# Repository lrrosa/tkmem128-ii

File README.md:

# TKMEM-128 II

Expansão externa de **128 KB (ou 512 KB) de RAM paginada no padrão ZX Spectrum 128**
para **TK90X, TK95 e ZX Spectrum 48K**. Redesenho completo em **KiCad 10**, com
arquivos de fabricação prontos.

> O nome vem da placa brasileira que originou este redesenho, mas o circuito é do
> **Velesoft e nasceu para o ZX Spectrum 48K**. A adaptação de 2012 ao TK usava um
> contato que no Spectrum carrega vídeo; aqui isso foi corrigido, e a placa voltou
> a servir nas duas famílias. Ver [Compatibilidade](#compatibilidade).

> **Estado: placas fabricadas e conferidas eletricamente, ainda não montadas.**
> ERC e DRC estão zerados, a netlist foi conferida contra a intenção de projeto,
> e as duas placas **voltaram da fábrica em setembro de 2026 com todas as ilhas
> aprovadas no teste de continuidade**. O que ainda não foi feito: **montar os
> componentes e ligar num micro real**. Antes de mandar fabricar, leia
> [`docs/ANTES-DE-FABRICAR.md`](docs/ANTES-DE-FABRICAR.md) — há itens que
> dependem de medir peças físicas.
>
> O conector de borda é o **TE/AMP 5645235**, de entrada vertical. As cotas do
> footprint saíram do desenho de cliente e estão no
> [datasheet arquivado](docs/), mas ninguém montou a peça ainda.

---

## Este projeto é uma derivação

Ele não inventa o circuito: junta e redesenha dois trabalhos anteriores.

| Origem | Autor | O que veio de lá |
| --- | --- | --- |
| [**external 128kb upgrade**](https://velesoft.speccy.cz/zx/external_128kb_upgrade/index.htm) (`zx48_to_128-EASY_3`), 2009 | **Velesoft** (Pavel Cimbal, República Tcheca) | O circuito base: as equações do GAL20V8, o latch da porta `0x7FFD` e o esquema de paginação da SRAM, incluindo a extensão de 512K |
| **TKMEM-128**, 2012 | **Luccas Eletrônica** (Eduardo Luccas, Brasil) | A adaptação ao TK90X/TK95: soquete de EPROM com a ROM do Spectrum 128, jumpers de seleção de ROM, a auto-desativação da RAM interna de 32K por um pino livre do barramento, e a divisão em placa principal + expansor |

Créditos também a **Flávio Matsumoto**, que sugeriu o circuito do Velesoft para
os TKs e identificou a caixa Patola PB 085/3, e a **Daniel Jose Viana
(danjovic)**, cujo trabalho documentou as cotas da placa para essa caixa.

E a [**goloskokovic/zx16to128upgrade**](https://github.com/goloskokovic/zx16to128upgrade),
que redistribui o material do Velesoft com o crédito devido. De lá vieram duas
coisas que não estavam aqui: os **pontos de desativação da RAM interna num ZX
Spectrum 48K**, por Issue de placa-mãe (ver
[`docs/PREPARAR-O-TK.md`](docs/PREPARAR-O-TK.md#e-num-zx-spectrum-48k)), e os
arquivos da variante **`EASY_6b`**, que permitiram comparar as duas versões do
circuito original (ver
[`docs/VELESOFT-EASY3-x-EASY6B.md`](docs/VELESOFT-EASY3-x-EASY6B.md)). Nenhum
desses dois foi verificado em bancada por nós.

Este redesenho é distribuído sob **CERN-OHL-S v2** (ver [LICENSE.txt](LICENSE.txt)),
uma licença *fortemente recíproca*: quem fabricar, modificar ou distribuir
precisa disponibilizar as fontes das modificações sob a mesma licença.

---

## O que a placa faz

O ZX Spectrum 128 difere do 48K em três coisas: 128K de RAM em 8 bancos de 16K,
o chip de som AY-3-8912, e o espelhamento da memória de vídeo ("shadow video").
Esta placa entrega **a primeira**. O som AY exige interface separada; o shadow
video é inviável numa interface externa, porque exigiria interceptar a RAM baixa
da ULA dentro do micro.

Na prática a grande maioria dos jogos de 128K funciona — a exceção são os poucos
títulos que dependem do shadow video.

### Mapa de memória

| Faixa | Quem responde |
| --- | --- |
| `0x0000-0x3FFF` | ROM — a interna do micro, ou a 27C256 da placa (jumper) |
| `0x4000-0x7FFF` | RAM baixa **interna do micro** (memória de vídeo da ULA). Não é decodificada aqui |
| `0x8000-0xBFFF` | SRAM externa, **banco 2 fixo** |
| `0xC000-0xFFFF` | SRAM externa, banco selecionado pela porta `0x7FFD` |

Como a SRAM externa cobre `0x8000-0xFFFF`, **os 32 KB superiores de RAM interna
precisam ser desativados** — é a única alteração necessária dentro do micro, e a
única coisa que difere entre TK e ZX Spectrum. Veja
[`docs/PREPARAR-O-TK.md`](docs/PREPARAR-O-TK.md).

> **Sobre a variante `EASY_6b` do Velesoft.** Circula junto com a nossa em
> outros repositórios, e é fácil confundir com uma versão melhor. Não é: a
> serigrafia da placa dela diz `MEMORY UPGRADE FOR ZX 16`. É para um Spectrum de
> **16 KB**, onde a RAM inteira vem de fora — por isso as equações dela também
> decodificam `0x4000-0x7FFF`. **Este projeto deriva da `EASY_3`**; a comparação
> completa, incluindo a conferência do nosso esquemático e do nosso layout contra
> os do Velesoft, está em
> [`docs/VELESOFT-EASY3-x-EASY6B.md`](docs/VELESOFT-EASY3-x-EASY6B.md).

### Porta 0x7FFD

Um `74HCT273` latcheia o barramento de dados quando o GAL detecta a escrita na
porta (`A15=0`, `A5=1`, `A1=0`, `/IORQ` e `/WR` ativos):

| Bit | Sinal | Função |
| --- | --- | --- |
| 0–2 | `BANK0..BANK2` | Banco de RAM em `0xC000` |
| 3 | `VRAM` | Shadow screen — latcheado, **sem uso** nesta arquitetura (disponível em TP1) |
| 4 | `ROMA14` | Seleciona a metade da 27C256 |
| 5 | `DIS128` | Trava a paginação até o reset |
| 6–7 | `BANK3..BANK4` | Extensão 512K (só no modo ZX512) |

A trava do bit 5 é elegante: `DIS128` entra na equação do clock do latch
(`CLK7FFD = ... + DIS128`), então ao ser setado o clock fica preso em nível alto
e o latch nunca mais é acionado.

---

## Compatibilidade

**TK90X, TK95 e ZX Spectrum 48K.** Não é uma promessa vaga: reduz-se a uma regra
que dá para verificar.

O barramento de expansão é o mesmo conector de 2×28 nas duas famílias, mas
**nove contatos não carregam a mesma coisa** em cada uma. Enquanto a placa não
tocar nenhum deles, ela serve nas duas:

| Contato | No TK90X/TK95 | No ZX Spectrum 48K |
| --- | --- | --- |
| 4 | +9 V | USS |
| 7 | N.C. | GND |
| 15 | GND | sinal |
| 16, 17, 18 | livres | **Y, V e U do vídeo componente** |
| 34, 35 | 12 V | difere |
| 37 | **+5 V** | **−5 V** |

Esta placa liga **34 dos 54 contatos, e nenhum é dessa lista.** Alimentação sai
dos contatos 3 (+5 V), 6 e 14 (GND), que são iguais nas duas máquinas.

A verificação é automática, para a afirmação não envelhecer:

```bash
python tools/confere_compatibilidade.py
```

Ele cruza a lista de divergências de `busdef.py` com os contatos que a netlist
realmente usa, e falha se algum aparecer.

> ⚠️ **O que ainda é específico de cada máquina: desativar a RAM interna de 32 KB.**
> Isso não é opcional — sem desativar, a memória do micro colide com a SRAM
> externa em `0x8000-0xFFFF`. No TK é um fio do contato 29 ao pino 10 do IC27;
> num Spectrum o ponto é outro e **depende da Issue da placa-mãe** — os dois
> procedimentos estão em
> [`docs/PREPARAR-O-TK.md`](docs/PREPARAR-O-TK.md#e-num-zx-spectrum-48k).
> Num Spectrum a placa não aciona nada pelo contato 29 — mas **não porque o
> contato seja diferente**: ele é N.C. nas duas máquinas. É porque o
> procedimento publicado para o Spectrum amarra o pino do mod ao +5 V do
> próprio CI, sem trazer fio até o conector. Levar o truque do TK para lá é a
> mesma topologia, e esbarra numa diferença *elétrica* —
> [analisada aqui](docs/PREPARAR-O-TK.md#dava-para-levar-a-auto-desativação-para-o-spectrum).
>
> Não montamos a placa num Spectrum: a compatibilidade acima é do barramento,
> conferida contato a contato, não de bancada — e o ponto interno do Spectrum
> vem de terceiros, também não verificado por nós.

---

## As duas placas

A placa de componentes fica **em pé** dentro da caixa. O conector de borda é
soldado **diretamente nela** — e como esse conector é de entrada vertical
(a placa que entra fica perpendicular à que segura o conector), a fenda dele cai
no plano horizontal e recebe a placa do micro.

Os terminais do conector são **retos** e atravessam a placa, sobrando ~3,18 mm
do outro lado em duas fileiras a 4,85 mm. A **tira de expansão** entra **entre
essas fileiras** — uma passa por cima dela, a outra por baixo — e é soldada
**dos dois lados**. Ela não tem conector nenhum: ilhas de solda nas duas faces
de um extremo, dedos de borda no outro.

O **conector fica fora da caixa Patola**, atravessando o recorte que se abre na
frente dela. Não é escolha estética: no TK e no ZX Spectrum a abertura
`EXPANSION` é **recuada dentro da carcaça**, então a caixa encosta na traseira do
micro e só o conector entra. A placa, por sua vez, assenta rente ao fundo da
caixa.

> No conector, **1..28 fica na fileira de baixo** (junto à aresta inferior da
> placa), igual à fileira inferior da placa do micro; 29..56 fica do lado de
> dentro. É a mesma convenção no TK e no ZX Spectrum, onde essas fileiras são
> chamadas de B e A.
>
> ⚠️ **O lado dos componentes tem que ficar virado para a tira de expansão**,
> nunca para o lado do conector. Ao contrário, a placa dentro da caixa esbarra
> no micro e não encaixa direito. Na prática o conector de borda é **o único
> componente do lado do cobre**: entra por baixo e é soldado por cima.

| Placa | Arquivo | Conteúdo |
| --- | --- | --- |
| Principal | [`hardware/tkmem128-ii.kicad_pro`](hardware/) | GAL20V8B, 74HCT273, SRAM DIP-32, EPROM 27C256, 3 jumpers, desacoplamento e o conector de borda |
| Tira de expansão | [`hardware/expansor/`](hardware/expansor/) | Ilhas de solda nas duas faces de um lado, dedos de borda do outro — nenhum componente, só o fio de terra `W1` |

A **placa principal é de 4 camadas**; a tira de expansão, de 2.

| Camada | Placa principal | Tira |
| --- | --- | --- |
| F.Cu | sinal | 27 retas de 1,5 mm (pinos 29..56) |
| In1.Cu | **plano de GND** inteiro | — |
| In2.Cu | **plano de +5V** inteiro | — |
| B.Cu | sinal | 27 retas de 1,5 mm (pinos 1..28) |

Como todos os componentes são passantes, cada ilha de `+5V` e de `GND` toca o seu
plano direto: **não há uma única trilha de alimentação nas faces de sinal**, e
nenhuma via serve só para alimentação. Sinal de 0,5 mm, isolação de 0,2 mm,
21 vias, e nenhum fio de ligação.

O furo grande no topo é o `H1`, e ele não é furo de parafuso: por ali **passa a
torre** de fixação da caixa Patola, que tem Ø5 externo e nasce do fundo da
tampa. O parafuso da caixa corre dentro da torre e nunca toca a placa — `H1`
serve para localizar, não para apertar.

O conector é passante e é usado pelos dois lados — por baixo entra o conector,
por cima solda a tira —, então a numeração dele está serigrafada nas duas
faces.

O verso é o manual da placa. Traz as **três tabelas de jumper**, a função do
`R4` e a licença — na bancada, com um shunt na pinça, isso vale mais que este
README.

A tira é soldada dos dois lados, então cada face traz a numeração dos **seus**
pinos: 29..56 na frente, 1..28 no verso.

### E fabricadas

Primeira tiragem, setembro de 2026. **Todas as ilhas passaram no teste de
continuidade** — as placas ainda não foram montadas nem ligadas num micro.

O verso cumpriu o que o render prometia: as três tabelas de jumper e a nota do
`R4` ficam legíveis a olho nu com a serigrafia de 1,2 mm — que é o ponto de
tê-las na placa em vez de só aqui.

A tira mostra os dois itens do formulário que **não viajam nos gerbers** (item 0
do [ANTES-DE-FABRICAR](docs/ANTES-DE-FABRICAR.md)) tendo saído certos: os dedos
vieram com **ENIG** e com o **chanfro de 45°**. O entalhe na borda de baixo, à
direita do centro, é o rasgo da guia — aprofundado de 5,0 para 7,0 mm depois da
conferência em papel.

---

## O que mudou em relação ao original

| Melhoria | Motivo |
| --- | --- |
| **Passagem do barramento** (dedos de borda na expansora) | O original ocupava o barramento; agora dá para encadear outros periféricos |
| **Desacoplamento por CI** (100 nF em cada um) + 10 µF de reservatório | O original tinha desacoplamento mínimo |
| **4 camadas com planos de GND e +5V inteiros** | Alimentação sem uma única trilha nas faces de sinal, retorno de corrente curto e imunidade a ruído. O original era de 2 camadas |
| **Jumper JP2 com duas estratégias de ROMCS** | O `ROMCS` do barramento é **ativo em nível alto** para desligar a ROM interna, o oposto da saída `/ROMCS` do GAL. É a explicação mais provável para a ROM 128 do original "funcionar num TK e não em outro". JP2 permite escolher entre acionar pelo GAL ou fixar em nível alto (como fazem os cartuchos da Interface 2), com R5 em série |
| **Auto-desativação sem jumper nenhum** | A original usava o **pino 17**, livre no TK mas **V do vídeo componente no ZX Spectrum** — daí o jumper e o aviso de que a posição errada danifica o micro. Aqui o sinal vai pelo **pino 29**, que é N.C. nas duas máquinas, então o pull-up é permanente e **JP4 deixou de existir**. Ver [a análise](docs/PREPARAR-O-TK.md#por-que-o-pino-29) |
| **GAL com `.jed` pronto e verificado** | O usuário não precisa montar nada: o `.jed` distribuído é gerado das equações deste projeto e conferido fusível a fusível contra o mapa de referência (checksum `C5752`, zero divergências) |
| **Degrau zero na corrente de periféricos** | A tira de expansão solda nos terminais do próprio conector, ficando coplanar com a placa do micro. O periférico seguinte entra no mesmo plano, sem escadinha |
| **Bit N da porta 7FFD no flip-flop N** | O original embaralhava as entradas do latch; aqui a ordem é natural e o esquemático se lê sozinho |
| **Endereços e dados da EPROM 1:1** | Obrigatório (o conteúdo da ROM é fixo) e documentado |
| **Pontos de teste** (`VRAM`, `CLK7FFD`) | Para depurar sem grampear em perna de CI |
| **LED de energia** (opcional) | Diagnóstico imediato |
| **Peças em produção na BOM** | AS6C1008 e ATF20V8B no lugar de peças só encontráveis como estoque antigo |

---

## Configuração dos jumpers

| Jumper | Posição | Efeito |
| --- | --- | --- |
| **JP1** SELECIONA ROM | 1-2 | ROM 128: a EPROM da placa responde em `0x0000-0x3FFF` |
| | 2-3 | ROM interna: EPROM desligada (padrão) |
| **JP2** ROMCS BARRAMENTO | aberto | Usa a ROM interna do micro (padrão) |
| | 1-2 | Aciona `ROMCS` pelo GAL (comportamento da placa original) |
| | 2-3 | Fixa `ROMCS` em nível alto (estilo Interface 2) |
| **JP3** ZX128/ZX512 | aberto | 128K — SRAM `AS6C1008` (padrão) |
| | fechado | 512K — SRAM `AS6C4008` |

Esta tabela está **serigrafada no verso da placa**, uma por jumper, com as
mesmas palavras — ver o render do verso acima.

> ⚠️ **JP1 em 1-2 sem JP2** não faz nada útil: sem desligar a ROM interna, os dois
> chips disputam o barramento de dados. Use os dois juntos ou nenhum.

> **A auto-desativação da RAM não tem jumper.** `R4` mantém o **pino 29** em
> nível 1 permanentemente, e esse pino é N.C. tanto no TK quanto no ZX Spectrum.
> Num Spectrum a placa não faz nada ali; num TK, com o fio interno do pino 29 ao
> pino 10 do IC27, ela desliga os 32 KB. Nada a configurar.

---

## Lista de material

### Placa principal

| Ref | Valor | Encapsulamento | Observação |
| --- | --- | --- | --- |
| U1 | GAL20V8B, **ATF20V8B-15PC** ou PALCE20V8H | DIP-24 300 mil | Grave [`hardware/gal/tkmem128.jed`](hardware/gal/tkmem128.jed) — peças equivalentes em [hardware/gal](hardware/gal/README.md) |
| U2 | 74HCT273 | DIP-20 300 mil | Latch da porta 7FFD |
| U3 | **AS6C1008-55PCN** (128K×8) | DIP-32 600 mil | Ou `AS6C4008-55PCN` (512K×8) no modo ZX512 — outras peças servem, ver [equivalentes](#equivalentes-para-u3-a-sram) |
| U4 | 27C256 | DIP-28 600 mil | **Opcional** — ver seção da ROM |
| R2, R4 | 1 kΩ | axial, vertical | |
| R5 | 0 Ω | axial, vertical | Fio; 100–470 Ω se houver disputa no ROMCS |
| R3 | 2,2 kΩ | axial, vertical | Opcional (LED) |
| C1–C5 | 100 nF cerâmico | disco 5 mm, passo 5 mm | |
| C6 | 10 µF eletrolítico | radial 5 mm, passo 2 mm | |
| D1 | LED 3 mm | | Opcional |
| JP1, JP2 | header 1×3 | passo 2,54 mm | |
| JP3 | header 1×2 | passo 2,54 mm | |
| J1 | **TE/AMP 5645235** — conector de borda 56 vias, entrada vertical | passo 2,54 mm, fileiras a 4,85 mm | Único componente do lado do cobre; recebe os dedos do micro |
| — | soquetes torneados DIP-20/24/28/32 | | Recomendado |

### Equivalentes para U3 (a SRAM)

O projeto não depende de um fabricante. Serve **qualquer SRAM 128K×8 de 5 V em
DIP-32 na pinagem JEDEC de 1 Mbit** — que é a pinagem padrão dessa família:
`/CS1` no 22, `/OE` no 24, `/WE` no 29, `CE2` no 30, `VCC` no 32, `GND` no 16.

| Peça | Fabricante | Situação |
| --- | --- | --- |
| **AS6C1008-55PCN** | Alliance | Da BOM — ainda em produção, a mais fácil de achar nova |
| **HM628128A** (ex.: `HM628128ALP-7`) | Hitachi | Descontinuada; comum como estoque antigo |
| **TC551001** | Toshiba | Descontinuada |
| **KM681000** | Samsung | Descontinuada |
| **CY62128** | Cypress | |
| **IS61C1024 / IS62C1024** | ISSI | O `1024` é 1024 kbit = 1 Mbit, não 1 M×8 |

> ⚠️ **Uma 62256 não serve.** É 32K×8 (256 kbit) em DIP-28 — outra
> capacidade e outro encapsulamento. A confusão é fácil porque a numeração
> parece próxima.

**A única divergência real entre essas peças é o pino 30**, e vale conferir no
datasheet da que você comprou:

| Pino 30 | Funciona? |
| --- | --- |
| `CE2` / `CS2`, ativo alto | **Sim** — é o caso da `AS6C1008` |
| `NC`, não conectado | **Sim** — o sinal é ignorado e o `/CS1` do pino 22 controla sozinho |
| `A17` | Aí é uma 512K×8, não uma 128K — ver abaixo |

Isso funciona porque `/SA17` é uma saída **invertida** do GAL:

```
/SA17 = A14 * A15 * BANK3 * /ZX512
```

Com **JP3 aberto**, o pull-up põe `ZX512` em alto, o produto zera e o pino 30
fica **fixo em nível alto** — exatamente o `CE2` que a memória espera.

> ⚠️ **Com uma 128K×8, JP3 fica aberto — sempre.** Fechado por engano, o
> pino 30 deixa de ser nível fixo e passa a receber `/SA17` paginado: toda vez
> que o software escrever `BANK3=1` na porta `0x7FFD`, o pino cai para nível
> baixo e **desabilita a RAM** em 0xC000. A falha é intermitente e depende do
> jogo, que é o pior tipo de falha para diagnosticar.

**Velocidade é indiferente.** Peças dessa família vão de 55 a 100 ns, e a
3,5 MHz há mais de 500 ns entre o endereço ficar válido e o Z80 amostrar o
dado. Até a mais lenta sobra.

**Procedência importa mais que velocidade.** As descontinuadas circulam como
estoque antigo e SRAM antiga é alvo comum de remarcação. Se o preço for
parecido, prefira a peça em produção.

#### No modo 512 KB

Aí a peça tem que ser uma **512K×8** de verdade — `AS6C4008`, `HM628512`,
`TC554001`, `IS61C4008` — porque o pino 30 passa a ser `A17` e o pino 1, `A18`.
E **JP3 fecha**. Ver [Modo 512 KB](docs/MONTAGEM.md#modo-512-kb).

### Tira de expansão

Não leva componente nenhum, nem conector: os "conectores" são cobre da própria
PCB, e o único item a soldar além das ilhas é um pedaço de fio.

| Ref | O que é | Observação |
| --- | --- | --- |
| J1 | Ilhas de solda nas duas faces, até a borda | Solda nos terminais retos do conector da placa principal, por cima e por baixo |
| J2 | Dedos de borda | Passagem do barramento ao próximo periférico |
| W1 | Fio isolado curto | Liga as duas ilhas `GND - FIO ISOLADO` no verso (pinos 6 e 14); passa por cima das trilhas, por isso isolado |

---

## Montagem

Guias detalhados:

- [`docs/PREPARAR-O-TK.md`](docs/PREPARAR-O-TK.md) — desativar a RAM interna de 32K
- [`docs/MONTAGEM.md`](docs/MONTAGEM.md) — ordem de montagem, guia do conector, caixa
- [`docs/ANTES-DE-FABRICAR.md`](docs/ANTES-DE-FABRICAR.md) — conferências obrigatórias
- [`docs/VELESOFT-EASY3-x-EASY6B.md`](docs/VELESOFT-EASY3-x-EASY6B.md) — as duas variantes do circuito original, e por que este projeto usa a `EASY_3`

Dois pontos que costumam pegar quem monta:

1. **A guia do conector de borda.** O conector de 56 vias vem sem guia. Na
   posição **5/52** você encaixa um pedacinho de PCB (ou material equivalente)
   casando com o rasgo entre os dedos do TK — a placa não tem furos ali,
   porque não há terminal nessa posição. Sem a guia é fácil plugar deslocado
   e danificar o micro.
2. **A tira de expansão é soldada dos dois lados.** Ela entra entre as duas
   fileiras de terminais retos do conector — uma fileira por cima, outra por
   baixo — e as ilhas chegam até a borda, então o terminal encontra cobre
   mesmo se for curto.

---

## Fabricação

Arquivos prontos em [`production/`](production/): Gerber X2, furação Excellon,
BOM e mapa de posições, para as duas placas.

Cada placa tem o seu `gerbers.zip`, que é o arquivo que se envia à fábrica.

| | Placa principal | Tira de expansão |
| --- | --- | --- |
| Camadas | **4** (F.Cu / GND / +5V / B.Cu) | **2** |
| Espessura | 1,6 mm | 1,6 mm |
| Trilha | 0,5 mm | 1,5 mm |
| Isolação | 0,2 mm | 0,25 mm |
| Furo mínimo | 0,3 mm | — (sem furos) |
| Via | 0,8 mm com furo de 0,4 mm | nenhuma |
| Furo não metalizado | 1 × Ø5,4 (`H1`, passagem da torre da caixa) | nenhum |

Tudo folgado dentro da capacidade padrão de fábrica barata — nada aqui entra em
faixa de preço especial, a não ser as 4 camadas da placa principal.

> ⚠️ **Peça 4 camadas para a placa principal.** Se pedir 2 por engano, a fábrica
> descarta os dois planos internos e a placa sai sem alimentação nenhuma — falha
> que não aparece na inspeção visual. Ver
> [ANTES-DE-FABRICAR, item 3b](docs/ANTES-DE-FABRICAR.md).

**A tira de expansão precisa de acabamento em ouro (ENIG) na placa inteira e
chanfro de 45° na borda dos dedos.** Os dedos entram e saem do conector do
periférico seguinte muitos ciclos, e as ilhas de solda do outro extremo também
chegam à borda — HASL descasca nos dois casos. Peça o chanfro explicitamente,
é um item à parte no pedido.

---

## Gravando o GAL

**Já vai pronto**: grave [`hardware/gal/tkmem128.jed`](hardware/gal/tkmem128.jed)
direto no programador. Checksum de fusíveis **`C5752`** — confira no software do
gravador ao abrir o arquivo.

Esse `.jed` não foi copiado de lugar nenhum: é gerado por
[`tools/galgen.py`](tools/galgen.py) a partir das equações deste projeto, e
conferido **fusível a fusível** contra o mapa de referência do projeto do
Velesoft — *zero divergências em 2706 fusíveis*. O fonte em sintaxe GALasm está
em [`tkmem128.pld`](hardware/gal/tkmem128.pld) para quem quiser modificar.

Programadores XGecu (T48/T56) gravam GAL20V8B, ATF20V8B e PALCE20V8H — mas
**escolha no software o dispositivo que você tem de verdade**: o mapa de
fusíveis é o mesmo, o algoritmo de gravação não.

---

## A ROM do Spectrum 128

**A imagem da ROM não está neste repositório** — ela é copyright da Amstrad/Sky.
O hardware (soquete U4 + jumpers) está lá; a imagem você monta com as suas
cópias de `128-0.rom` e `128-1.rom`:

```bash
cat 128-0.rom 128-1.rom > rom_tkmem128_27c256.bin
```

A ordem importa: `A14` da EPROM vem de `ROMA14` (bit 4 da porta 7FFD), então a
ROM 0 (editor do 128) tem que ficar na metade baixa.

Vale dizer que **a ROM é dispensável**: o autor da TKMEM-128 original deixou de
fornecê-la depois de constatar que os jogos de 128K não dependem dela, e que ela
causava incompatibilidades entre unidades diferentes de TK90X.

---

## Estrutura do repositório

```
hardware/
  tkmem128-ii.kicad_pro/.kicad_sch/.kicad_pcb   placa principal
  expansor/                                   tira de expansão
  lib/                                        símbolos e footprints próprios
  gal/                                        fonte e documentação do GAL
production/
  placa-principal/                            gerbers, furação, BOM, posições, PDF
  tira-expansao/                            idem
docs/
  PREPARAR-O-TK.md   MONTAGEM.md   ANTES-DE-FABRICAR.md
  VELESOFT-EASY3-x-EASY6B.md                  comparação com a variante do autor original
  relatorios/                                 saídas de ERC e DRC
tools/                                        geradores do projeto KiCad
```

A biblioteca de símbolos e footprints é **local ao projeto** — nada depende da
versão das bibliotecas do seu KiCad.

O projeto KiCad **nasceu gerado por script** a partir de uma descrição única da
netlist ([`tools/`](tools/)) — é o que garante que esquemático e placa não
divergem — e depois foi refinado à mão no KiCad. A fonte corrente são os
arquivos em `hardware/`; os geradores ficam como registro e ferramenta de apoio.

### Estado da verificação

| Placa | ERC | DRC | Ligações |
| --- | --- | --- | --- |
| Principal | 0 | 0 erros (6 avisos cosméticos) | 0 pendentes |
| Tira de expansão | 0 | 0 erros (4 avisos cosméticos) | 0 pendentes |

A netlist exportada pelo KiCad foi comparada nó a nó com a intenção de projeto
nas duas placas: **74 nets na principal e 53 na tira, zero divergência**.

---

## Licença

Hardware sob **CERN-OHL-S v2** — ver [LICENSE.txt](LICENSE.txt).

```
Copyright Leonardo Rosa e contribuidores.
Derivado de: "external 128kb upgrade" (Velesoft, 2009)
             TKMEM-128 (Luccas Eletrônica, 2012)

Este código-fonte é licenciado sob CERN-OHL-S v2 ou posterior.
Você pode redistribuí-lo e modificá-lo nos termos dessa licença.
Distribuído SEM QUALQUER GARANTIA, incluindo as de COMERCIALIZAÇÃO,
ADEQUAÇÃO A UM FIM ESPECÍFICO E NÃO-VIOLAÇÃO.
Consulte a CERN-OHL-S v2 para os termos aplicáveis.
```

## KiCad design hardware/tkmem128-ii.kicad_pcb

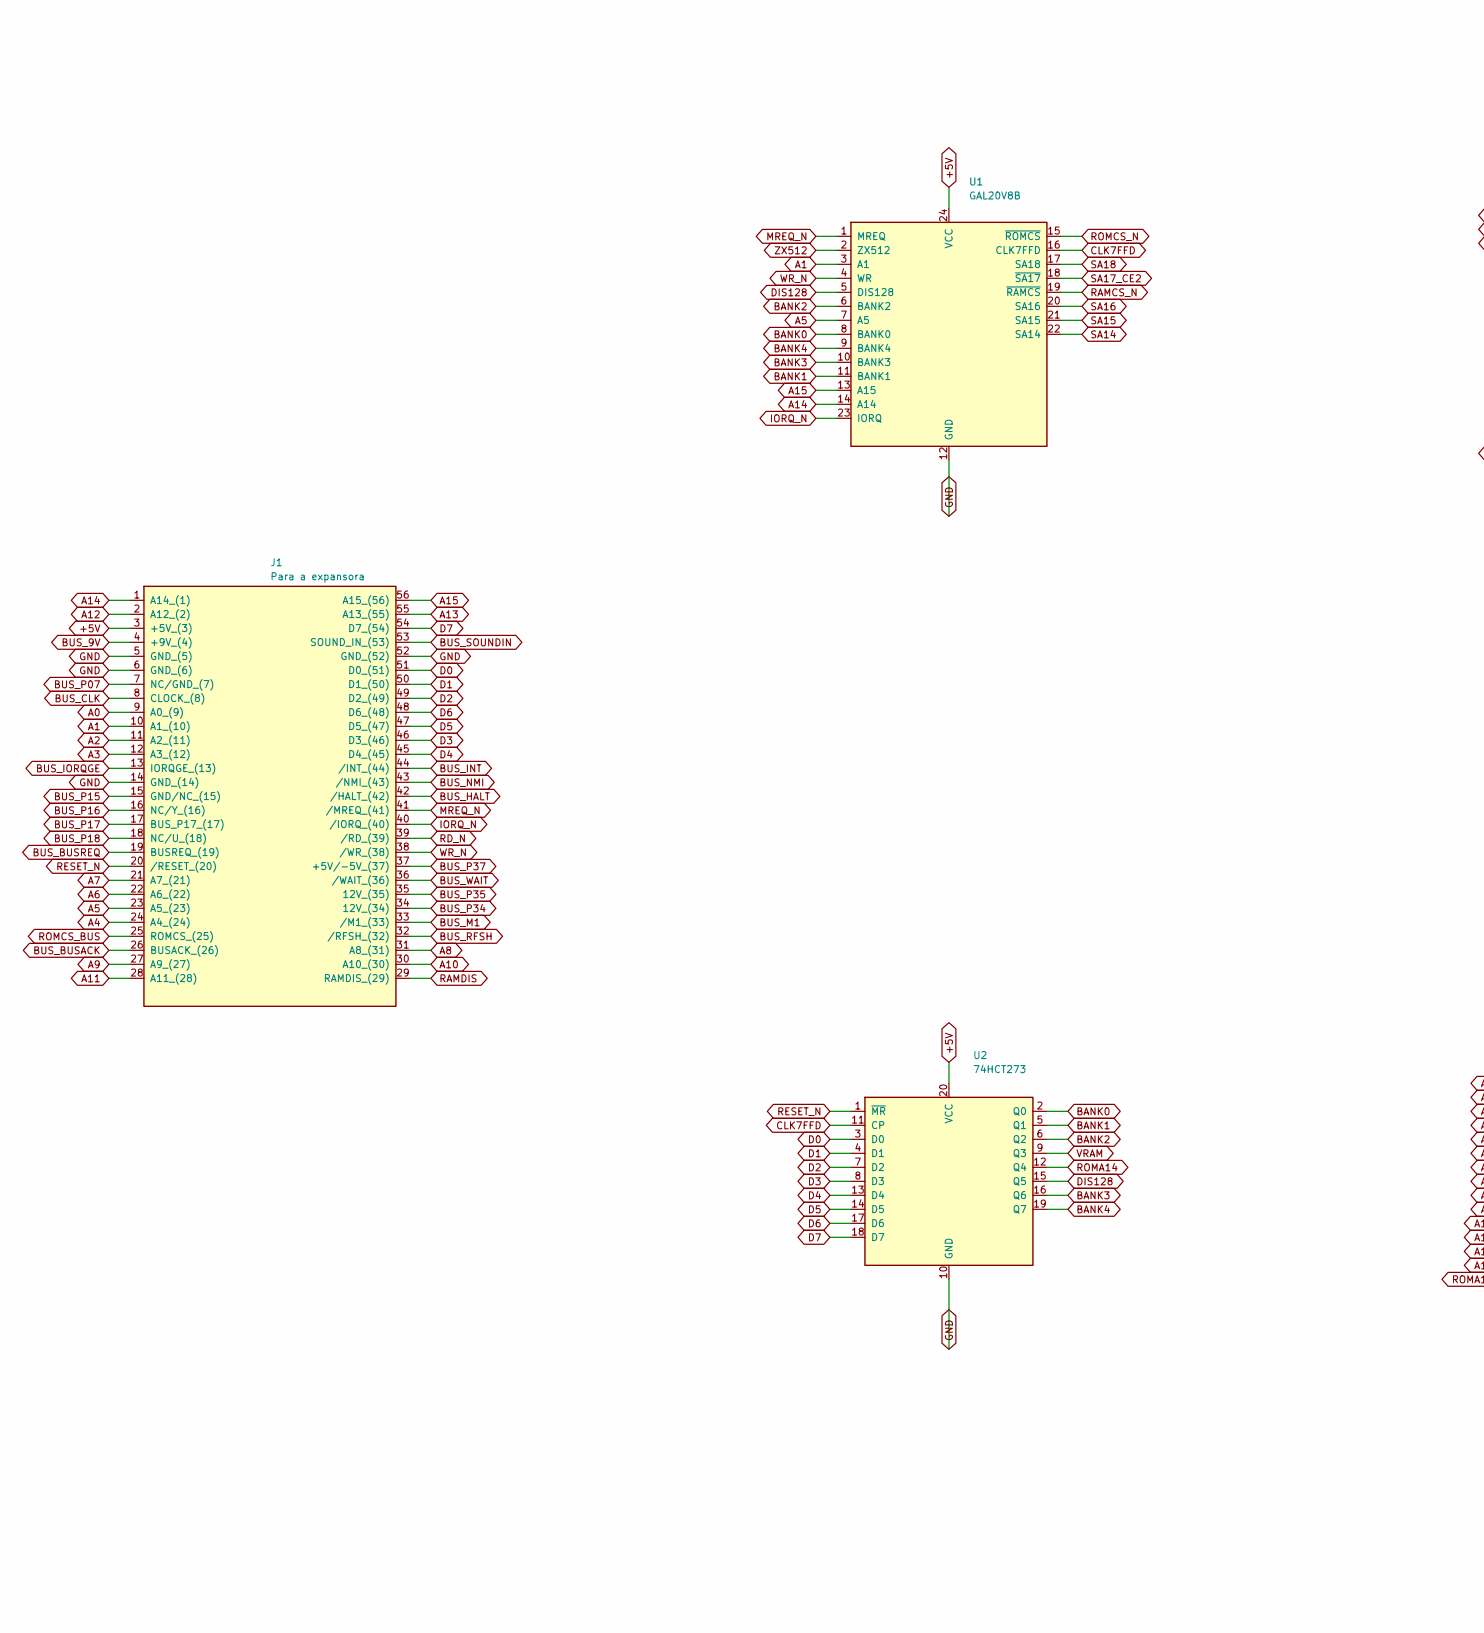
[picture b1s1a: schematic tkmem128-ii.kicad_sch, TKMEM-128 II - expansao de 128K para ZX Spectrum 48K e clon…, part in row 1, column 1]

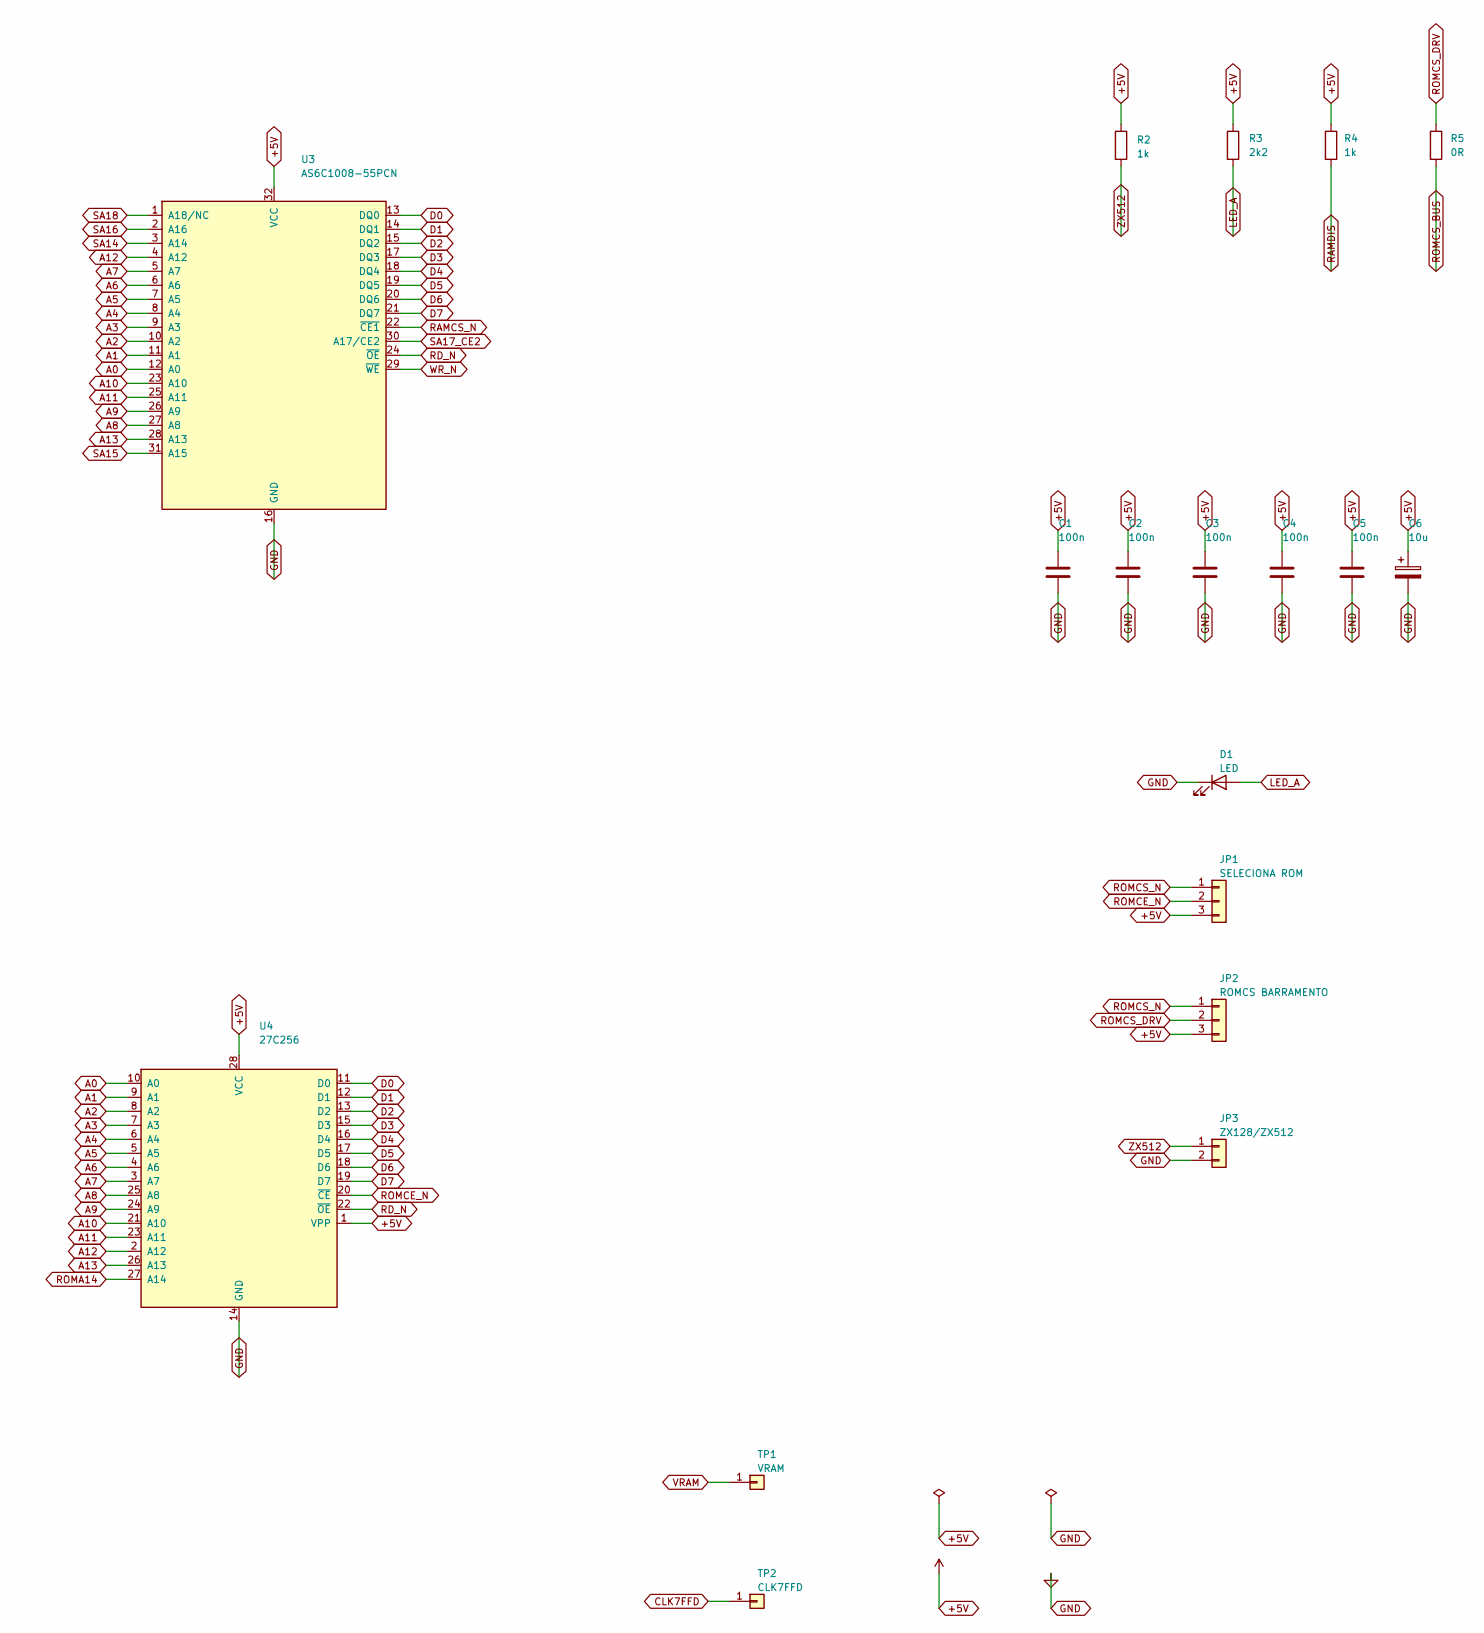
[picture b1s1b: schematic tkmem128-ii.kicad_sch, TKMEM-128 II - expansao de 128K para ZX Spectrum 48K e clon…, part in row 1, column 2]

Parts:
C1, C2, C3, C4, C5: 100n; C_Disc_D5.0mm_W2.5mm_P5.00mm
C6: 10u; CP_Radial_D5.0mm_P2.00mm
D1: LED; LED_D3.0mm
J1: Para a expansora; ZX_TK_Bus_Header_2x28
JP1: SELECIONA ROM; PinHeader_1x03_P2.54mm_Vertical
JP2: ROMCS BARRAMENTO; PinHeader_1x03_P2.54mm_Vertical
JP3: ZX128/ZX512; PinHeader_1x02_P2.54mm_Vertical
R2, R4: 1k; R_Axial_DIN0207_L6.3mm_D2.5mm_P2.54mm_Vertical
R3: 2k2; R_Axial_DIN0207_L6.3mm_D2.5mm_P2.54mm_Vertical
R5: 0R; R_Axial_DIN0207_L6.3mm_D2.5mm_P2.54mm_Vertical
TP1: VRAM; TestPoint_THTPad_D1.5mm_Drill0.7mm
TP2: CLK7FFD; TestPoint_THTPad_D1.5mm_Drill0.7mm
U1: GAL20V8B; DIP-24_W7.62mm_Socket_LongPads
U2: 74HCT273; DIP-20_W7.62mm_Socket_LongPads
U3: AS6C1008-55PCN; DIP-32_W15.24mm_Socket_LongPads
U4: 27C256; DIP-28_W15.24mm_Socket_LongPads

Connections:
+5V: C1.1, C2.1, C3.1, C4.1, C5.1, C6.1, J1.3 (+5V_(3)), JP1.3, JP2.3, R2.1, R3.1, R4.1, U1.24 (VCC), U2.20 (VCC), U3.32 (VCC), U4.1 (VPP), U4.28 (VCC)
A0: J1.9 (A0_(9)), U3.12 (A0), U4.10 (A0)
A1: J1.10 (A1_(10)), U1.3 (A1), U3.11 (A1), U4.9 (A1)
A2: J1.11 (A2_(11)), U3.10 (A2), U4.8 (A2)
A3: J1.12 (A3_(12)), U3.9 (A3), U4.7 (A3)
A4: J1.24 (A4_(24)), U3.8 (A4), U4.6 (A4)
A5: J1.23 (A5_(23)), U1.7 (A5), U3.7 (A5), U4.5 (A5)
A6: J1.22 (A6_(22)), U3.6 (A6), U4.4 (A6)
A7: J1.21 (A7_(21)), U3.5 (A7), U4.3 (A7)
A8: J1.31 (A8_(31)), U3.27 (A8), U4.25 (A8)
A9: J1.27 (A9_(27)), U3.26 (A9), U4.24 (A9)
A10: J1.30 (A10_(30)), U3.23 (A10), U4.21 (A10)
A11: J1.28 (A11_(28)), U3.25 (A11), U4.23 (A11)
A12: J1.2 (A12_(2)), U3.4 (A12), U4.2 (A12)
A13: J1.55 (A13_(55)), U3.28 (A13), U4.26 (A13)
A14: J1.1 (A14_(1)), U1.14 (A14)
A15: J1.56 (A15_(56)), U1.13 (A15)
BANK0: U1.8 (BANK0), U2.2 (Q0)
BANK1: U1.11 (BANK1), U2.5 (Q1)
BANK2: U1.6 (BANK2), U2.6 (Q2)
BANK3: U1.10 (BANK3), U2.16 (Q6)
BANK4: U1.9 (BANK4), U2.19 (Q7)
BUS_9V: J1.4 (+9V_(4))
BUS_BUSACK: J1.26 (BUSACK_(26))
BUS_BUSREQ: J1.19 (BUSREQ_(19))
BUS_CLK: J1.8 (CLOCK_(8))
BUS_HALT: J1.42 (/HALT_(42))
BUS_INT: J1.44 (/INT_(44))
BUS_IORQGE: J1.13 (IORQGE_(13))
BUS_M1: J1.33 (/M1_(33))
BUS_NMI: J1.43 (/NMI_(43))
BUS_P07: J1.7 (NC/GND_(7))
BUS_P15: J1.15 (GND/NC_(15))
BUS_P16: J1.16 (NC/Y_(16))
BUS_P17: J1.17 (BUS_P17_(17))
BUS_P18: J1.18 (NC/U_(18))
BUS_P34: J1.34 (12V_(34))
BUS_P35: J1.35 (12V_(35))
BUS_P37: J1.37 (+5V/-5V_(37))
BUS_RFSH: J1.32 (/RFSH_(32))
BUS_SOUNDIN: J1.53 (SOUND_IN_(53))
BUS_WAIT: J1.36 (/WAIT_(36))
CLK7FFD: TP2.1, U1.16 (CLK7FFD), U2.11 (CP)
D0: J1.51 (D0_(51)), U2.3 (D0), U3.13 (DQ0), U4.11 (D0)
D1: J1.50 (D1_(50)), U2.4 (D1), U3.14 (DQ1), U4.12 (D1)
D2: J1.49 (D2_(49)), U2.7 (D2), U3.15 (DQ2), U4.13 (D2)
D3: J1.46 (D3_(46)), U2.8 (D3), U3.17 (DQ3), U4.15 (D3)
D4: J1.45 (D4_(45)), U2.13 (D4), U3.18 (DQ4), U4.16 (D4)
D5: J1.47 (D5_(47)), U2.14 (D5), U3.19 (DQ5), U4.17 (D5)
D6: J1.48 (D6_(48)), U2.17 (D6), U3.20 (DQ6), U4.18 (D6)
D7: J1.54 (D7_(54)), U2.18 (D7), U3.21 (DQ7), U4.19 (D7)
DIS128: U1.5 (DIS128), U2.15 (Q5)
GND: C1.2, C2.2, C3.2, C4.2, C5.2, C6.2, D1.1 (K), J1.5 (GND_(5)), J1.6 (GND_(6)), J1.14 (GND_(14)), J1.52 (GND_(52)), JP3.2, U1.12 (GND), U2.10 (GND), U3.16 (GND), U4.14 (GND)
IORQ_N: J1.40 (/IORQ_(40)), U1.23 (IORQ)
LED_A: D1.2 (A), R3.2
MREQ_N: J1.41 (/MREQ_(41)), U1.1 (MREQ)
RAMCS_N: U1.19 (~RAMCS), U3.22 (~CE1)
RAMDIS: J1.29 (RAMDIS_(29)), R4.2
RD_N: J1.39 (/RD_(39)), U3.24 (~OE), U4.22 (~OE)
RESET_N: J1.20 (/RESET_(20)), U2.1 (~MR)
ROMA14: U2.12 (Q4), U4.27 (A14)
ROMCE_N: JP1.2, U4.20 (~CE)
ROMCS_BUS: J1.25 (ROMCS_(25)), R5.2
ROMCS_DRV: JP2.2, R5.1
ROMCS_N: JP1.1, JP2.1, U1.15 (~ROMCS)
SA14: U1.22 (SA14), U3.3 (A14)
SA15: U1.21 (SA15), U3.31 (A15)
SA16: U1.20 (SA16), U3.2 (A16)
SA17_CE2: U1.18 (~SA17), U3.30 (A17/CE2)
SA18: U1.17 (SA18), U3.1 (A18/NC)
VRAM: TP1.1, U2.9 (Q3)
WR_N: J1.38 (/WR_(38)), U1.4 (WR), U3.29 (~WE)
ZX512: JP3.1, R2.2, U1.2 (ZX512)

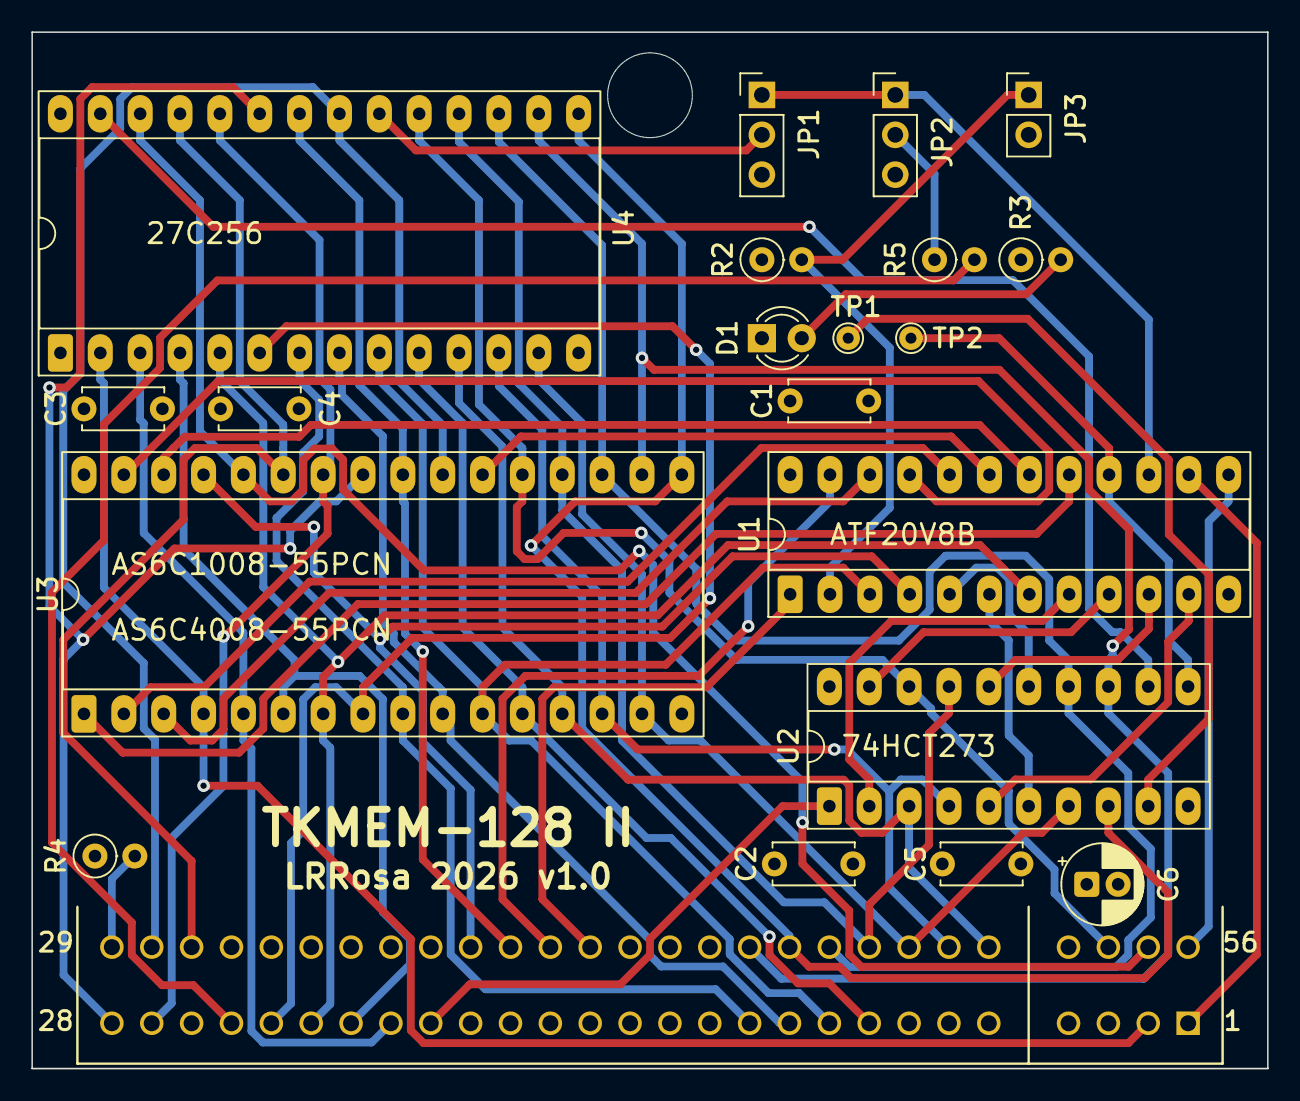
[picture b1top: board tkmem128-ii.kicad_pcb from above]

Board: 4 copper layers, 78.7 x 66.0 mm, 22 parts (1 on the bottom side), 53 nets.

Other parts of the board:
H1: MountingHole_5.4mm

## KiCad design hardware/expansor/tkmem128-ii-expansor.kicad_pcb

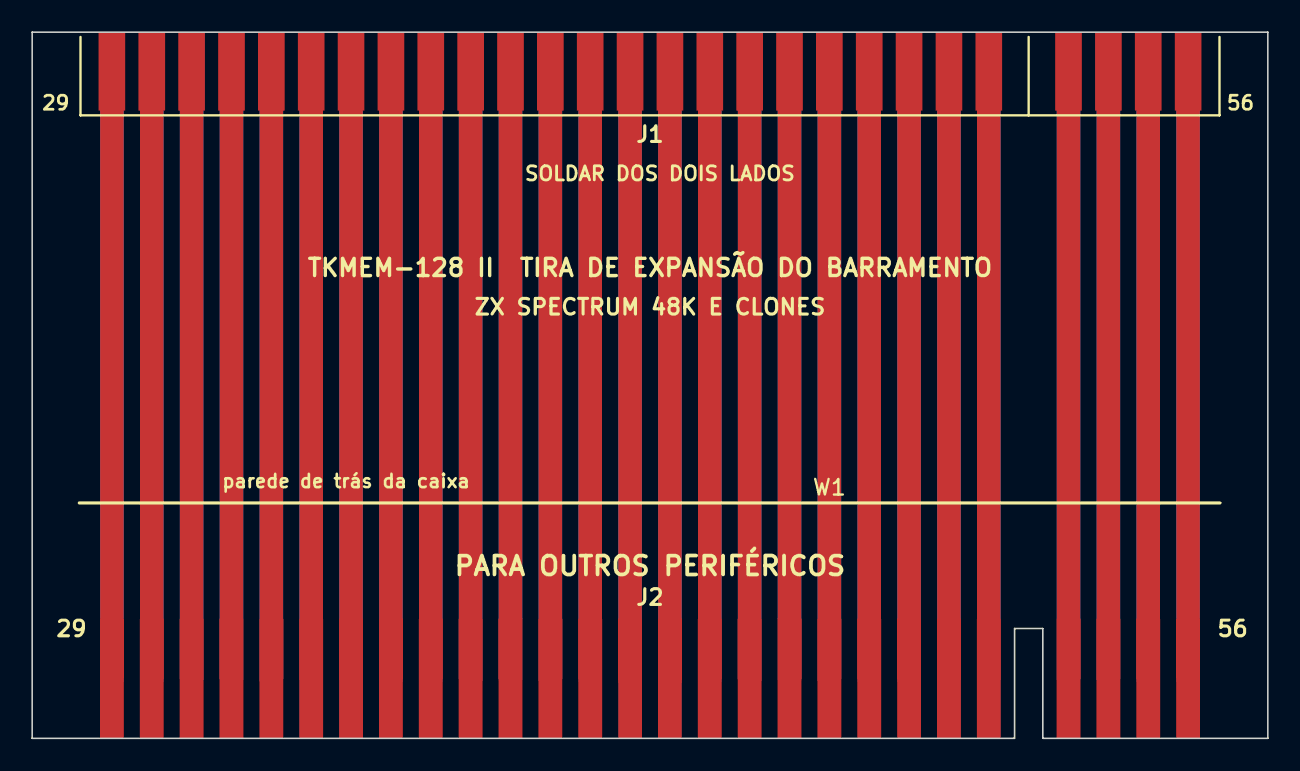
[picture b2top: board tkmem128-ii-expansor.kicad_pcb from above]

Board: 2 copper layers, 78.7 x 45.0 mm, 3 parts (0 on the bottom side), 53 nets.

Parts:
J1: Terminais do conector; ZX_TK_Bus_SolderPads_56
J2: Passagem; ZX_TK_Bus_Fingers_56
W1: WireLink_GND_P20.32mm

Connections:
+5V: J1.3, J2.3
A0: J1.9, J2.9
A1: J1.10, J2.10
A2: J1.11, J2.11
A3: J1.12, J2.12
A4: J1.24, J2.24
A5: J1.23, J2.23
A6: J1.22, J2.22
A7: J1.21, J2.21
A8: J1.31, J2.31
A9: J1.27, J2.27
A10: J1.30, J2.30
A11: J1.28, J2.28
A12: J1.2, J2.2
A13: J1.55, J2.55
A14: J1.1, J2.1
A15: J1.56, J2.56
BUS_9V: J1.4, J2.4
BUS_BUSACK: J1.26, J2.26
BUS_BUSREQ: J1.19, J2.19
BUS_CLK: J1.8, J2.8
BUS_HALT: J1.42, J2.42
BUS_INT: J1.44, J2.44
BUS_IORQGE: J1.13, J2.13
BUS_M1: J1.33, J2.33
BUS_NMI: J1.43, J2.43
BUS_P07: J1.7, J2.7
BUS_P15: J1.15, J2.15
BUS_P16: J1.16, J2.16
BUS_P18: J1.18, J2.18
BUS_P29: J1.29, J2.29
BUS_P34: J1.34, J2.34
BUS_P35: J1.35, J2.35
BUS_P37: J1.37, J2.37
BUS_RFSH: J1.32, J2.32
BUS_SOUNDIN: J1.53, J2.53
BUS_WAIT: J1.36, J2.36
D0: J1.51, J2.51
D1: J1.50, J2.50
D2: J1.49, J2.49
D3: J1.46, J2.46
D4: J1.45, J2.45
D5: J1.47, J2.47
D6: J1.48, J2.48
D7: J1.54, J2.54
GND: J1.6, J1.14, J2.6, J2.14, W1.1
IORQ_N: J1.40, J2.40
MREQ_N: J1.41, J2.41
RAMDIS: J1.17, J2.17
RD_N: J1.39, J2.39
RESET_N: J1.20, J2.20
ROMCS_BUS: J1.25, J2.25
WR_N: J1.38, J2.38

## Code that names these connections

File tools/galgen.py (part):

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    return total & 0xFFFF


PINNAMES = ("MREQ:1 ZX512:2 A1:3 WR:4 DIS128:5 BANK2:6 A5:7 BANK0:8 "
            "BANK4:9 BANK3:10 BANK1:11 GND:12 A15:13 A14:14 ROMCS:15 "
            "CLK7FFD:16 SA18:17 SA17:18 RAMCS:19 SA16:20 SA15:21 SA14:22 "
            "IORQ:23 VCC:24")
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

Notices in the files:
hardware/expansor/tkmem128-ii-expansor.kicad_pcb:
CERN-OHL-S v2  |  github.com/lrrosa/tkmem128-ii
hardware/tkmem128-ii.kicad_sch:
Derivado de Velesoft (2009) e Luccas Eletronica (2012) - CERN-OHL-S v2
